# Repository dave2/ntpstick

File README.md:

ntpstick
========

NTPstick is a GPS-synced NTP server designed for low cost and ease
of deployment in places outside traditional datacentres.

The "stick" concept is that the board is expected to be placed into
a PVC tube at least 30mm I.D. with only an Ethernet cable reaching
the outside world carrying both Ethernet and poor-mans POE.

Structure
---------

This repo is divided into sections for different parts of the project:

 - hardware/ .. Contains the Kicad sources, schematics in PDF, and generated
   gerber files.
 - firmware/ .. Completed builds of the firmware, able to be flashed to 
   boards over TFTP
 - src/ .. Source code for the firmware.

Specifications
--------------

 - u.fl GPS antenna connection
 - uBlox MAX-M8Q GPS module (includes internal TCXO)
 - Atmel ATXMEGA128A4U MCU
 - 27MHz VCXO system clock
 - 12-bit DAC for VCXO control
 - WizNet W5500 Ethernet/IP chip
 - DC input on spare Ethernet pairs
 - DC-DC first stage, linear second stage PSU
 - Board is 113mm long, 30mm wide
 
License
-------

 - Please check each folder for the specific license applied, as they
   vary between sections of the project.

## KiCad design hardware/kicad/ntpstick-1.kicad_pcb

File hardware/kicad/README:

Notes on Kicad source files for NTPstick
========================================

- These files require the current upstream source of Kicad to be read.
  In general, versions shipped with most distributions are not new 
  enough to read these files. At least r5256 is required from the Kicad
  source repo.

- I have not included separate libraries or footprints that were created
  for this project. I'll include them at some future point.

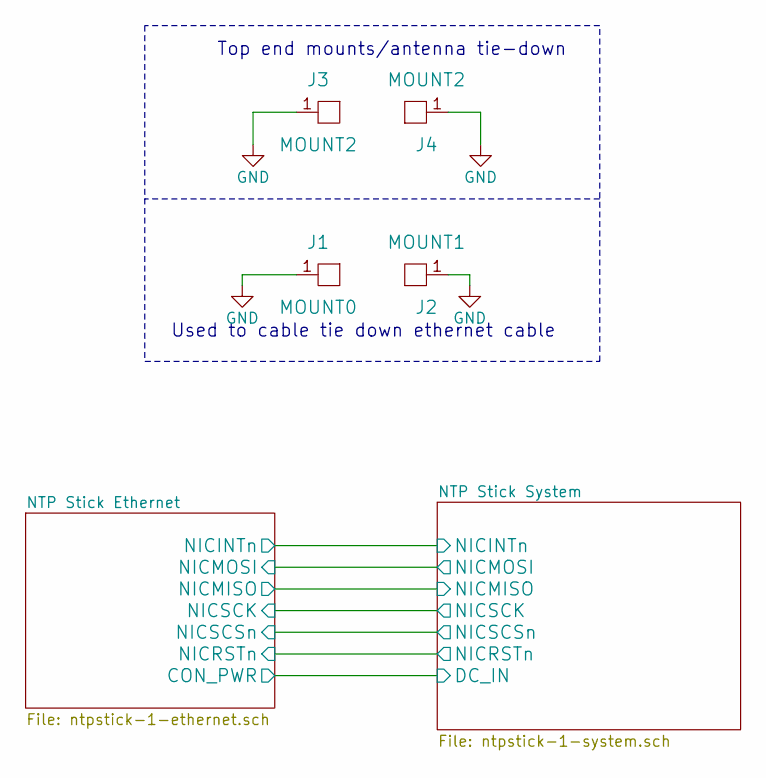
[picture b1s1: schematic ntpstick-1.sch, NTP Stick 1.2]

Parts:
J1: MOUNT0; 4-40-HOLE
J2: MOUNT1; 4-40-HOLE
J3, J4: MOUNT2; 4-40-HOLE

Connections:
GND: J1.1, J2.1, J3.1, J4.1; also elsewhere on the board

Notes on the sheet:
Used to cable tie down ethernet cable
Top end mounts/antenna tie-down

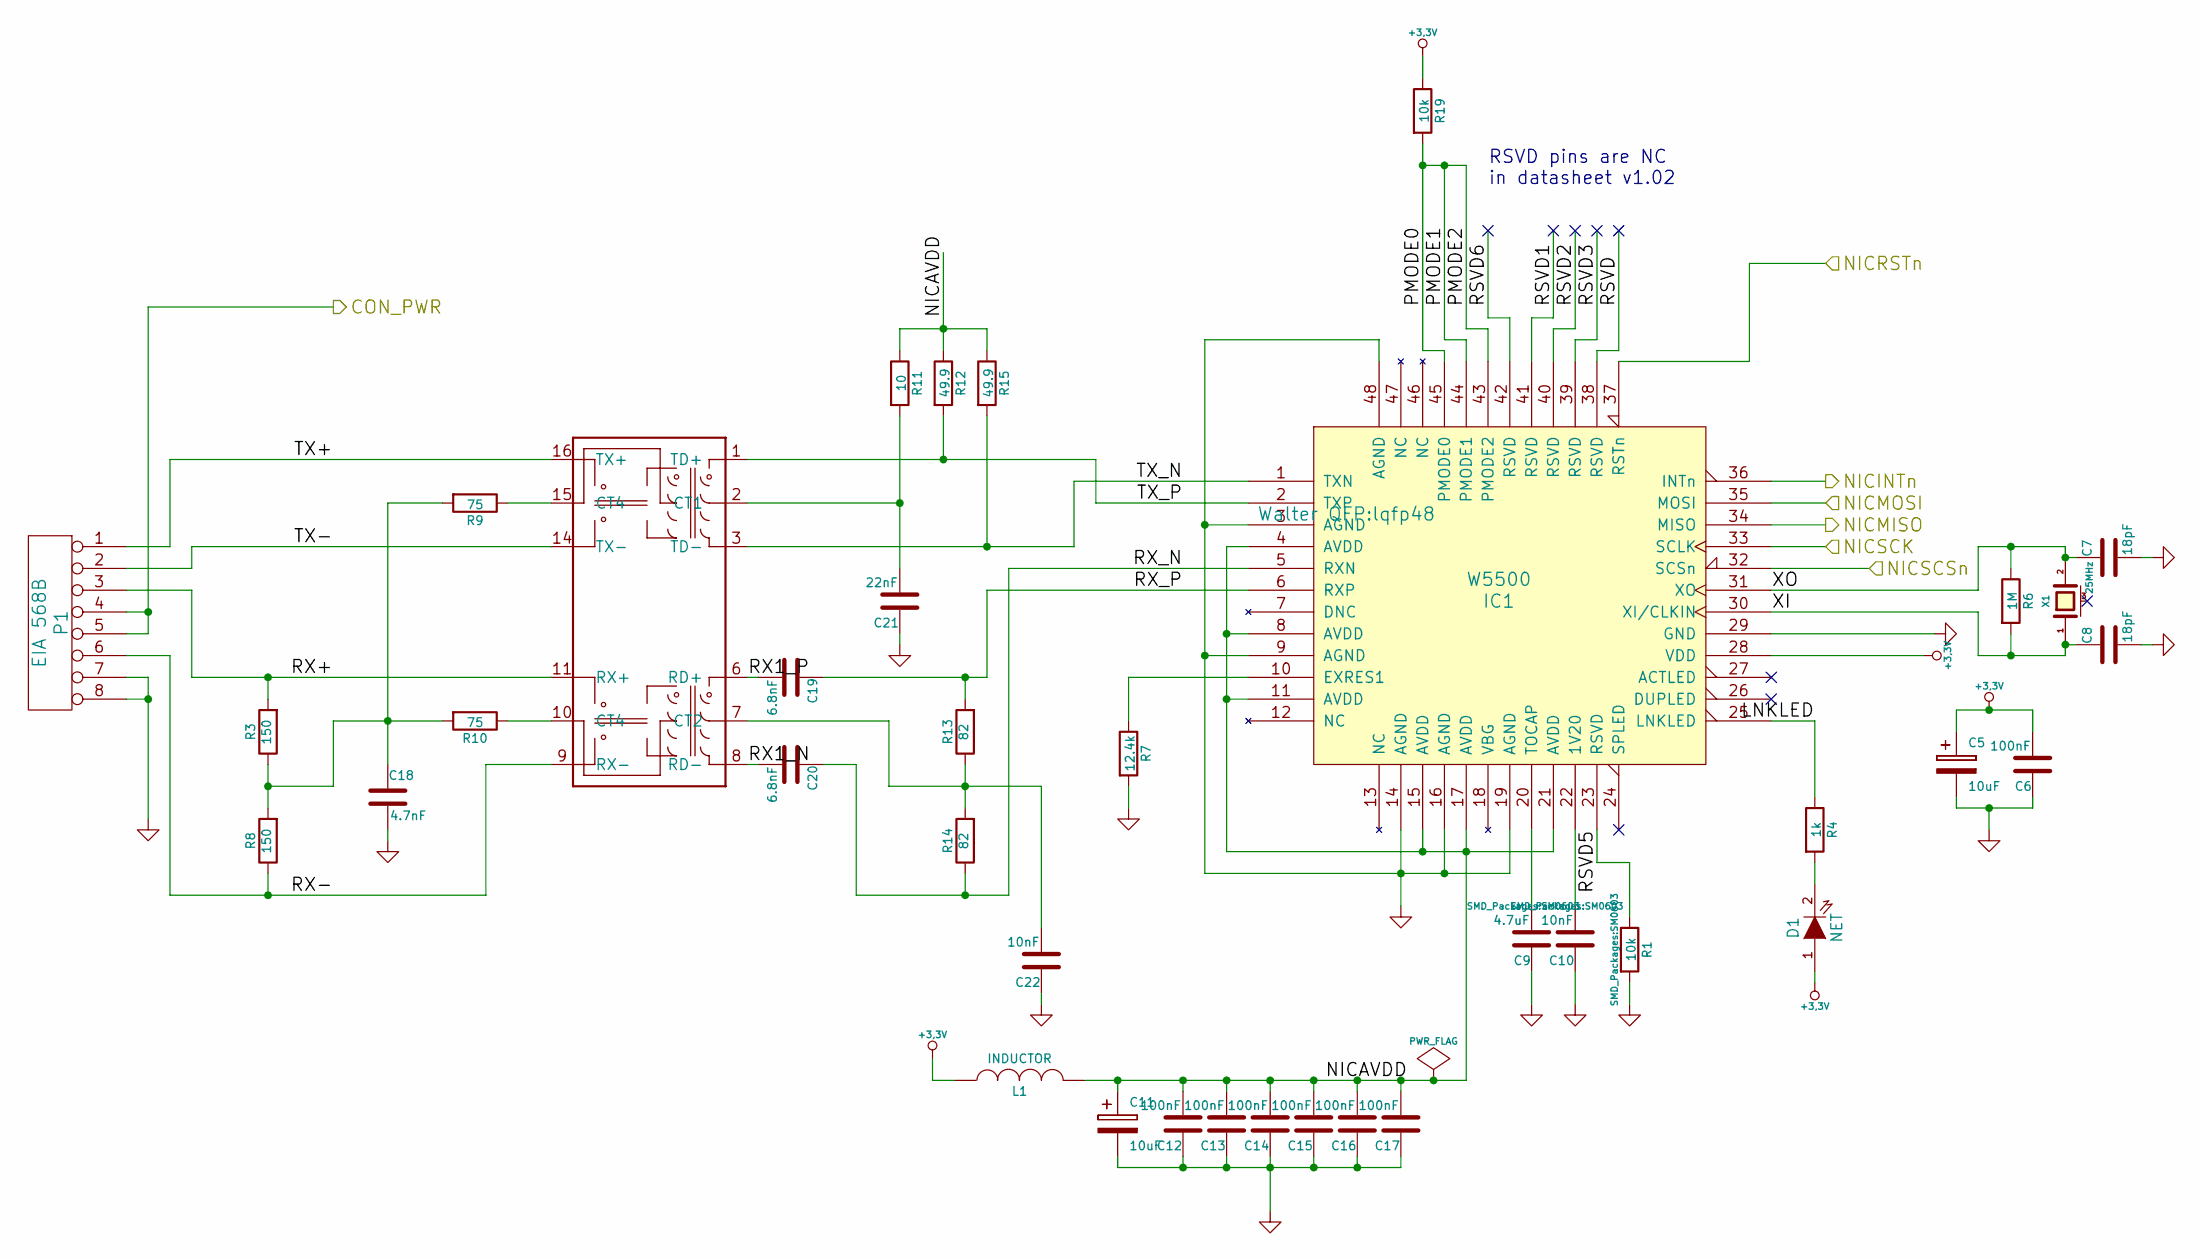
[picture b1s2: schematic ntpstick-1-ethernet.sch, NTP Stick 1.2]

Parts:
C5, C11: 10uF; c_tant_A; Voltage 16V
C6, C12, C13, C14, C15, C16, C17: 100nF; SM0603
C7, C8: 18pF; SM0603
C9: 4.7uF; SM0603
C10, C22: 10nF; SM0603
C18: 4.7nF; SM1812; Voltage 2kV
C19, C20: 6.8nF; SM0603
C21: 22nF; SM0603
D1: NET; LED-0805
IC1: W5500; lqfp48
L1: INDUCTOR; SM0603
P1: EIA 568B; pin_strip_8
R1, R19: 10k; SM0603
R3, R8: 150; SM0603
R4: 1k; SM0603
R6: 1M; SM0603
R7: 12.4k; SM0603
R9, R10: 75; SM0603
R11: 10; SM0603
R12, R15: 49.9; SM0603
R13, R14: 82; SM0603
U1: TG110-E*N5_N5; N5
X1: 25MHz; crystal_smd_5x3.2mm

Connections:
+3.3V: C5.1, C6.2, D1.1 (A), IC1.28 (VDD), L1.1, R19.1; also elsewhere on the board
/NTP Stick Ethernet/CON_PWR: P1.4, P1.5; also elsewhere on the board
/NTP Stick Ethernet/LNKLED: IC1.25 (LNKLED), R4.1
/NTP Stick Ethernet/NICAVDD: C11.1, C12.2, C13.2, C14.2, C15.2, C16.2, C17.2, IC1.4 (AVDD), IC1.8 (AVDD), IC1.11 (AVDD), IC1.15 (AVDD), IC1.17 (AVDD), IC1.21 (AVDD), L1.2, R11.1, R12.1, R15.1
/NTP Stick Ethernet/NICINTn: IC1.36 (INTn); also elsewhere on the board
/NTP Stick Ethernet/NICMISO: IC1.34 (MISO); also elsewhere on the board
/NTP Stick Ethernet/NICMOSI: IC1.35 (MOSI); also elsewhere on the board
/NTP Stick Ethernet/NICRSTn: IC1.37 (RSTn); also elsewhere on the board
/NTP Stick Ethernet/NICSCK: IC1.33 (SCLK); also elsewhere on the board
/NTP Stick Ethernet/NICSCSn: IC1.32 (SCSn); also elsewhere on the board
/NTP Stick Ethernet/PMODE0: IC1.43 (PMODE2), IC1.44 (PMODE1), IC1.45 (PMODE0), R19.2
/NTP Stick Ethernet/RSVD: IC1.38 (RSVD)
/NTP Stick Ethernet/RSVD1: IC1.41 (RSVD)
/NTP Stick Ethernet/RSVD2: IC1.40 (RSVD)
/NTP Stick Ethernet/RSVD3: IC1.39 (RSVD)
/NTP Stick Ethernet/RSVD5: IC1.23 (RSVD), R1.1
/NTP Stick Ethernet/RSVD6: IC1.42 (RSVD)
/NTP Stick Ethernet/RX1_N: C20.2, U1.8 (RD-)
/NTP Stick Ethernet/RX1_P: C19.2, U1.6 (RD+)
/NTP Stick Ethernet/RX+: P1.3, R3.2, U1.11 (RX+)
/NTP Stick Ethernet/RX-: P1.6, R8.1, U1.9 (RX-)
/NTP Stick Ethernet/RX_N: C20.1, IC1.5 (RXN), R14.1
/NTP Stick Ethernet/RX_P: C19.1, IC1.6 (RXP), R13.2
/NTP Stick Ethernet/TX+: P1.1, U1.16 (TX+)
/NTP Stick Ethernet/TX-: P1.2, U1.14 (TX-)
/NTP Stick Ethernet/TX_N: IC1.1 (TXN), R15.2, U1.3 (TD-)
/NTP Stick Ethernet/TX_P: IC1.2 (TXP), R12.2, U1.1 (TD+)
/NTP Stick Ethernet/XI: C8.1, IC1.30 (XI/CLKIN), R6.2, X1.1
/NTP Stick Ethernet/XO: C7.1, IC1.31 (XO), R6.1, X1.2
GND: C5.2, C6.1, C7.2, C8.2, C9.1, C10.1, C11.2, C12.1, C13.1, C14.1, C15.1, C16.1, C17.1, C18.2, C21.1, C22.1, IC1.3 (AGND), IC1.9 (AGND), IC1.14 (AGND), IC1.16 (AGND), IC1.19 (AGND), IC1.29 (GND), IC1.48 (AGND), P1.7, P1.8, R1.2, R7.2; also elsewhere on the board
unnamed: C9.2, IC1.20 (TOCAP)
unnamed: C10.2, IC1.22 (1V20)
unnamed: C18.1, R3.1, R8.2, R9.2, R10.2
unnamed: C21.2, R11.2, U1.2 (CT1)
unnamed: C22.2, R13.1, R14.2, U1.7 (CT2)
unnamed: D1.2 (K), R4.2
unnamed: IC1.10 (EXRES1), R7.1
unnamed: R9.1, U1.15 (CT4)
unnamed: R10.1, U1.10 (CT4)

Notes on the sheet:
RSVD pins are NC in datasheet v1.02

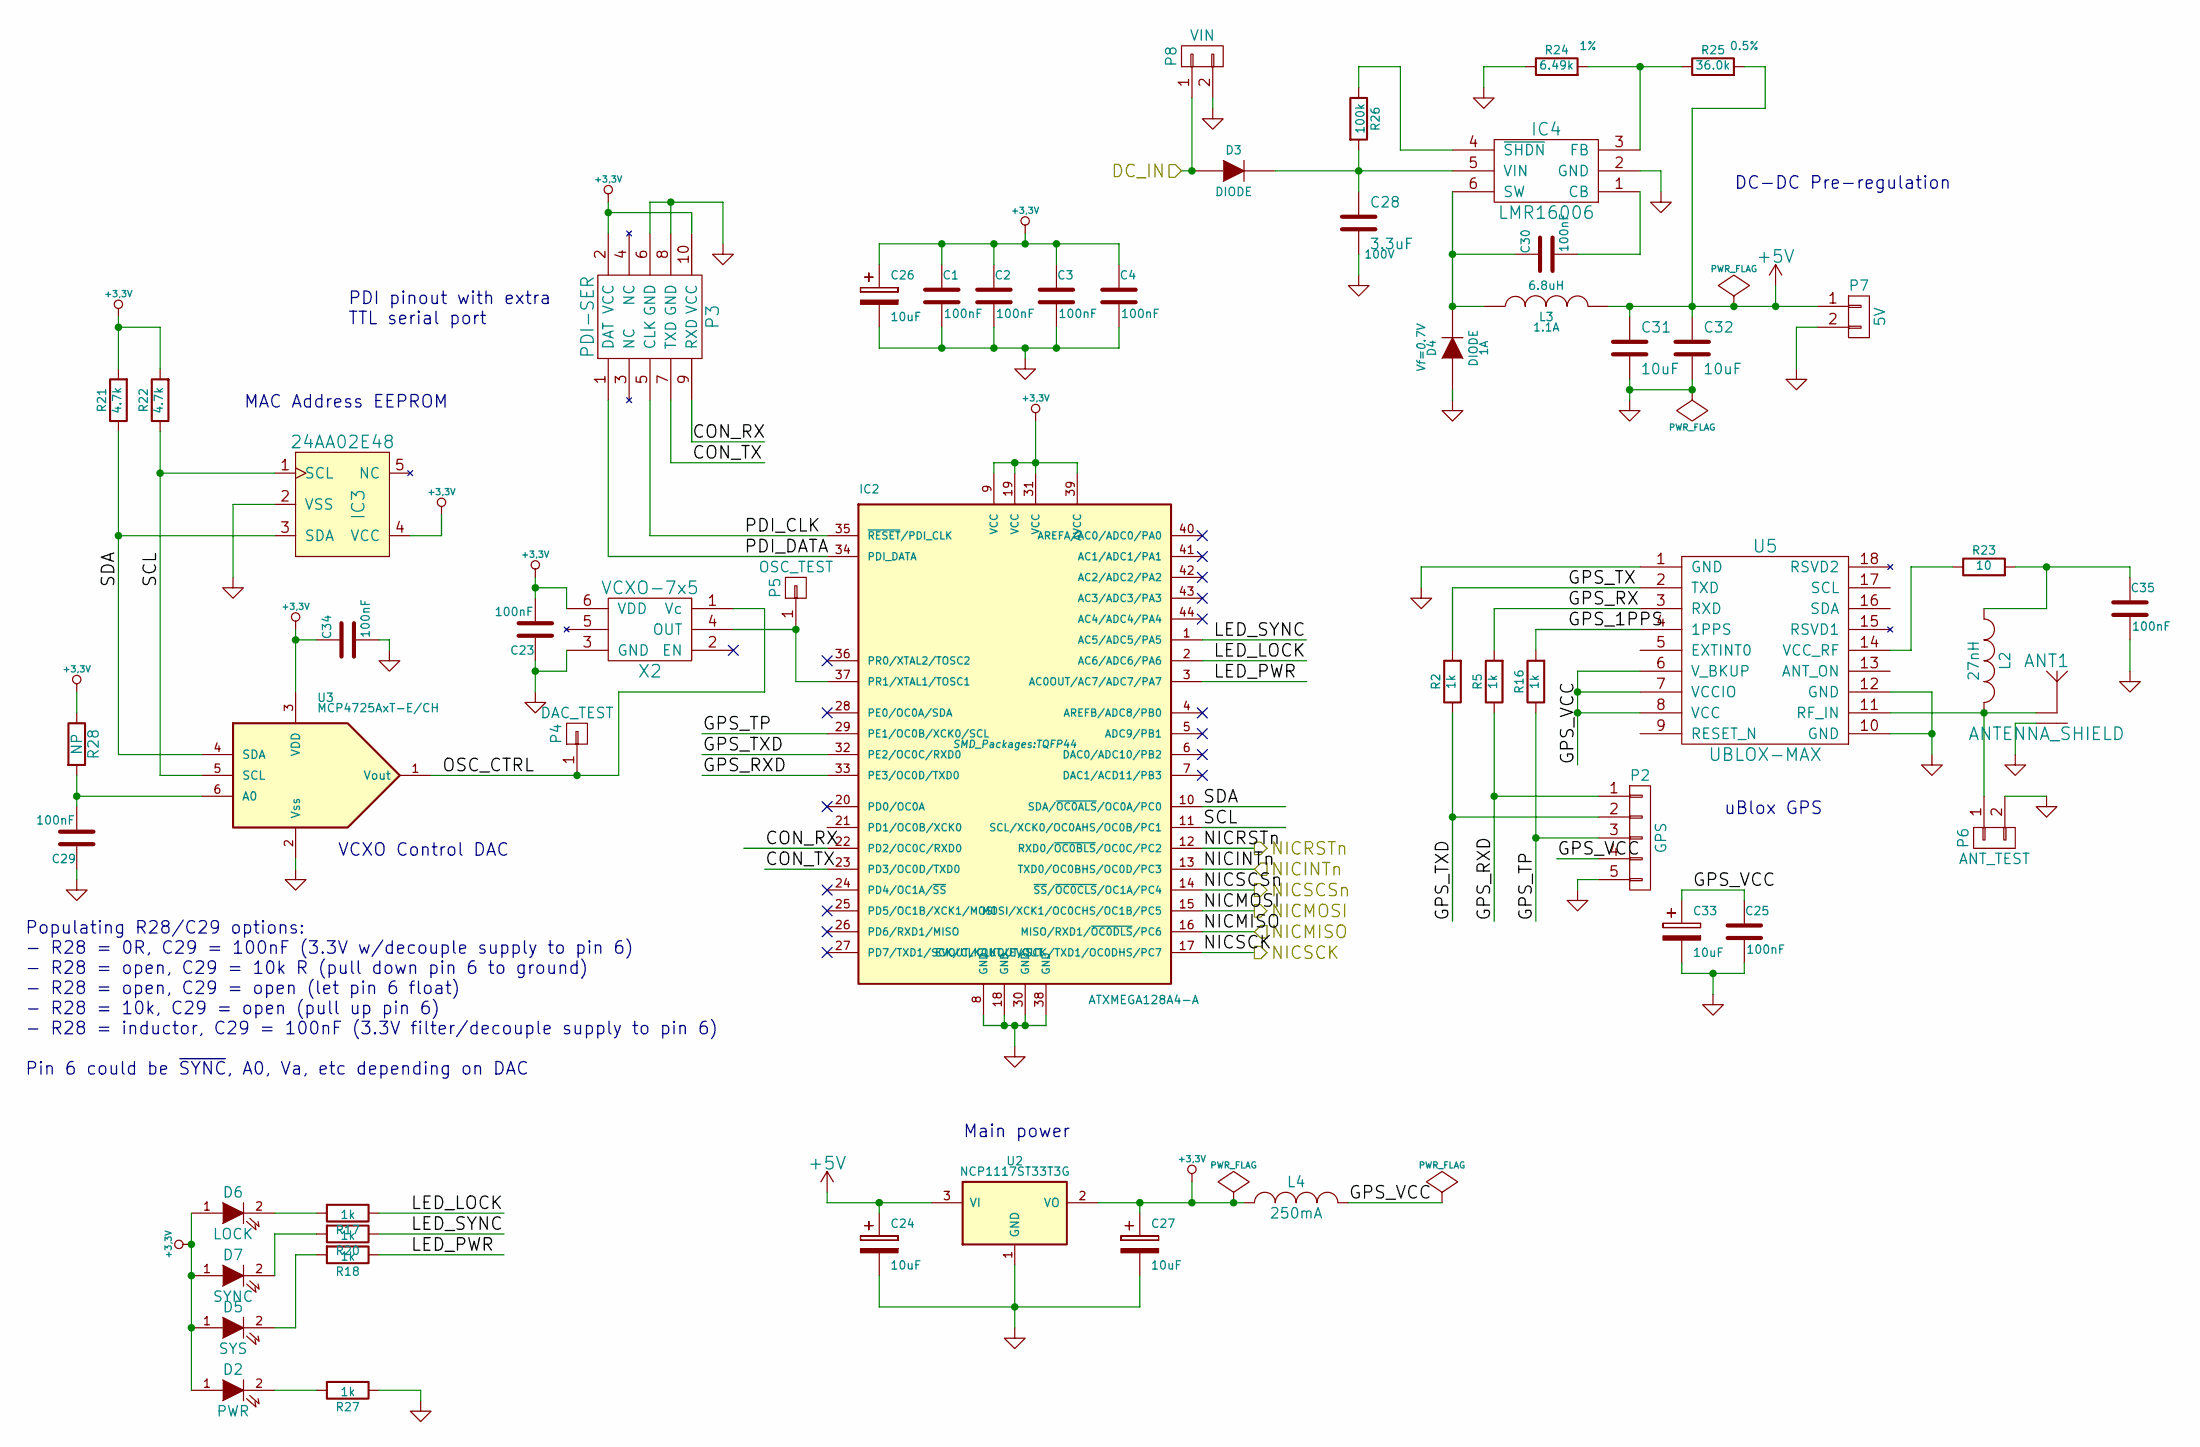
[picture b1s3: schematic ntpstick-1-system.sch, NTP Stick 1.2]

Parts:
ANT1: ANTENNA_SHIELD; coaxial_u.fl-r-smt-1
C1, C2, C3, C4, C23, C25, C29, C30, C34, C35: 100nF; SM0603
C24, C26, C27, C33: 10uF; c_tant_A; Voltage 16V
C28: 3.3uF; SM1210; Voltage 100V
C31, C32: 10uF; c_1206
D2: PWR; LED-0805
D3, D4: DIODE; do214ac
D5: SYS; LED-0805
D6: LOCK; LED-0805
D7: SYNC; LED-0805
IC2: ATXMEGA128A4-A; TQFP44
IC3: 24AA02E48; SOT23-5
IC4: LMR16006; SOT23_6
L2: 27nH; SM0603
L3: 6.8uH; inductor_bourns_srn5040
L4: 250mA; SM0603
P2: GPS; Pin_Header_Straight_1x05
P3: PDI-SER; Pin_Header_Straight_2x05
P4: DAC_TEST; Measurement_Point_Round-SMD-Pad_Small
P5: OSC_TEST; Measurement_Point_Round-SMD-Pad_Small
P6: ANT_TEST; Pin_Header_Straight_1x02
P7: 5V; Pin_Header_Straight_1x02
P8: VIN; Pin_Header_Straight_1x02
R2, R5, R16, R17, R18, R20, R27: 1k; SM0603
R21, R22: 4.7k; SM0603
R23: 10; SM0603
R24: 6.49k; SM0603
R25: 36.0k; SM0603
R26: 100k; SM0603
R28: NP; SM0603
U2: NCP1117ST33T3G; SOT223
U3: MCP4725AxT-E/CH; SOT23_6
U5: UBLOX-MAX; UBLOX-MAX-8-POLY
X2: VCXO-7x5; vcxo-7x5

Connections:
+3.3V: C1.1, C2.1, C3.1, C4.1, C23.2, C26.1, C27.1, C34.1, D2.1 (A), D5.1 (A), D6.1 (A), D7.1 (A), IC2.9 (VCC), IC2.19 (VCC), IC2.31 (VCC), IC2.39 (AVCC), IC3.4 (VCC), L4.1, P3.2 (VCC), P3.10 (VCC), R21.2, R22.2, R28.1, U2.2 (VO), U3.3 (VDD), X2.6 (VDD); also elsewhere on the board
+5V: C24.1, C31.1, C32.1, L3.2, P7.1, R25.2, U2.3 (VI)
/NTP Stick Ethernet/CON_PWR: D3.1 (A), P8.1; also elsewhere on the board
/NTP Stick Ethernet/NICINTn: IC2.13 (TXD0/OC0BHS/OC0D/PC3); also elsewhere on the board
/NTP Stick Ethernet/NICMISO: IC2.16 (MISO/RXD1/~OC0DLS~/PC6); also elsewhere on the board
/NTP Stick Ethernet/NICMOSI: IC2.15 (MOSI/XCK1/OC0CHS/OC1B/PC5); also elsewhere on the board
/NTP Stick Ethernet/NICRSTn: IC2.12 (RXD0/~OC0BLS~/OC0C/PC2); also elsewhere on the board
/NTP Stick Ethernet/NICSCK: IC2.17 (EVOUT/CLKOUT/SCK/TXD1/OC0DHS/PC7); also elsewhere on the board
/NTP Stick Ethernet/NICSCSn: IC2.14 (~SS~/~OC0CLS~/OC1A/PC4); also elsewhere on the board
/NTP Stick System/CON_RX: IC2.22 (PD2/OC0C/RXD0), P3.9 (RXD)
/NTP Stick System/CON_TX: IC2.23 (PD3/OC0D/TXD0), P3.7 (TXD)
/NTP Stick System/GPS_1PPS: R16.2, U5.4 (1PPS)
/NTP Stick System/GPS_RX: R5.2, U5.3 (RXD)
/NTP Stick System/GPS_RXD: IC2.33 (PE3/OC0D/TXD0), P2.1, R5.1
/NTP Stick System/GPS_TP: IC2.29 (PE1/OC0B/XCK0/SCL), P2.3, R16.1
/NTP Stick System/GPS_TX: R2.2, U5.2 (TXD)
/NTP Stick System/GPS_TXD: IC2.32 (PE2/OC0C/RXD0), P2.2, R2.1
/NTP Stick System/GPS_VCC: C25.1, C33.1, L4.2, P2.4, U5.6 (V_BKUP), U5.7 (VCCIO), U5.8 (VCC)
/NTP Stick System/LED_LOCK: IC2.2 (AC6/ADC6/PA6), R17.1
/NTP Stick System/LED_PWR: IC2.3 (AC0OUT/AC7/ADC7/PA7), R18.1
/NTP Stick System/LED_SYNC: IC2.1 (AC5/ADC5/PA5), R20.1
/NTP Stick System/OSC_CTRL: P4.1, U3.1 (Vout), X2.1 (Vc)
/NTP Stick System/PDI_CLK: IC2.35 (~RESET~/PDI_CLK), P3.5 (CLK)
/NTP Stick System/PDI_DATA: IC2.34 (PDI_DATA), P3.1 (DAT)
/NTP Stick System/SCL: IC2.11 (SCL/XCK0/OC0AHS/OC0B/PC1), IC3.1 (SCL), R22.1, U3.5 (SCL)
/NTP Stick System/SDA: IC2.10 (SDA/~OC0ALS~/OC0A/PC0), IC3.3 (SDA), R21.1, U3.4 (SDA)
GND: ANT1.2, C1.2, C2.2, C3.2, C4.2, C23.1, C24.2, C25.2, C26.2, C27.2, C28.2, C29.1, C31.2, C32.2, C33.2, C34.2, C35.2, D4.1 (A), IC2.8 (GND), IC2.18 (GND), IC2.30 (GND), IC2.38 (GND), IC3.2 (VSS), IC4.2 (GND), P2.5, P3.6 (GND), P3.8 (GND), P6.2, P7.2, P8.2, R24.1, R27.1, U2.1 (GND), U3.2 (Vss), U5.1 (GND), U5.10 (GND), U5.12 (GND), X2.3 (GND); also elsewhere on the board
unnamed: ANT1.1, L2.2, P6.1, U5.11 (RF_IN)
unnamed: C28.1, D3.2 (K), IC4.5 (VIN), R26.2
unnamed: C29.2, R28.2, U3.6 (A0)
unnamed: C30.1, D4.2 (K), IC4.6 (SW), L3.1
unnamed: C30.2, IC4.1 (CB)
unnamed: C35.1, L2.1, R23.2
unnamed: D2.2 (K), R27.2
unnamed: D5.2 (K), R18.2
unnamed: D6.2 (K), R17.2
unnamed: D7.2 (K), R20.2
unnamed: IC2.37 (PR1/XTAL1/TOSC1), P5.1, X2.4 (OUT)
unnamed: IC4.3 (FB), R24.2, R25.1
unnamed: IC4.4 (~SHDN~), R26.1
unnamed: R23.1, U5.14 (VCC_RF)

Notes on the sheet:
MAC Address EEPROM
VCXO Control DAC
DC-DC Pre-regulation
PDI pinout with extra TTL serial port
Main power
uBlox GPS
Populating R28/C29 options: - R28 = 0R, C29 = 100nF (3.3V w/decouple supply to pin 6) - R28 = open, C29 = 10k R (pull down pin 6 to ground) - R28 = open, C29 = open (let pin 6 float) - R28 = 10k, C29 = open (pull up pin 6) - R28 = inductor, C29 = 100nF (3.3V filter/decouple supply to pin 6) Pin 6 c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

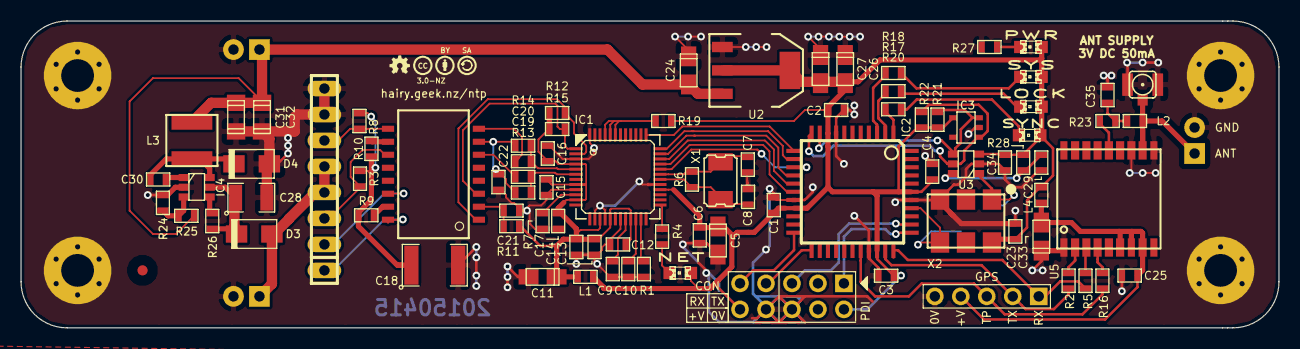
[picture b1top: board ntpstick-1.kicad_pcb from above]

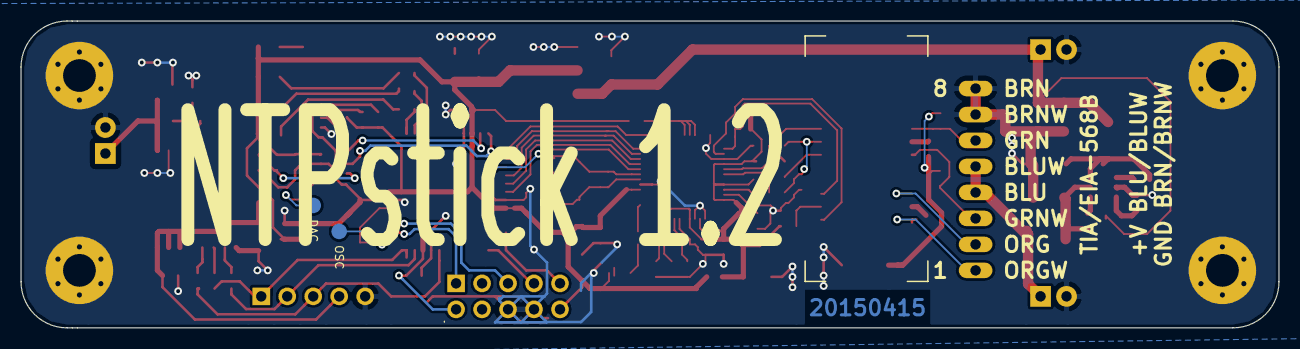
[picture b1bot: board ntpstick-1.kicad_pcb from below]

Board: 2 copper layers, 123.0 x 30.0 mm, 103 parts (3 on the bottom side), 66 nets.

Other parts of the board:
FIDUCIAL: val**; FIDUCIAL
LOGO_CC: VAL**; LOGO_CC_1.9mm
LOGO_CC_BY: VAL**; LOGO_CC_BY_1.9mm
LOGO_CC_SA: VAL**; LOGO_CC_SA_1.9mm
LOGO_OSHW_silkscreen_2mm: val**; LOGO_OSHW_silkscreen_2mm
SERIAL_LABEL: VAL**; SERIAL_LABEL

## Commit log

2014-11-10 Add more details about the project
2014-11-10 Clean up .gitignore, removing some files which will be required for hardware design.
2014-11-10 Initial cut of hardware source files
2014-11-10 Gerbers most recently generated.
2014-11-10 License and README for gerbers
2014-11-10 License and README for Kicad Source files
2014-11-10 Add schematic as PDF
2014-11-10 Also add some details on structure
2014-11-10 How about some dimensions as well.
2014-11-11 Gerbers sent for panelisation on 20141111
2014-11-11 libkakapo base for ntpstick development Explanation of source structure and build requirements
2014-11-11 Fix some typos in ntpstick source readme
2014-11-11 Really simple hack to build libkakapo and then ntpstick objects
2014-11-14 Add codeblocks stuff to ignore filter
2014-11-15 Inital rough test of console over serial.
2014-11-16 Network config, eeprom setup, provide firmware build date in boot scrawl
2014-11-16 Very rudimentary console over telnet support. Not fully working yet.
2014-12-13 Add initial breakout of telnetd support, incl. commands
2014-12-13 Switch to single event handler in driver code. This resyncs us with libkakapo mainline
2014-12-13 Various changes, mostly around getting telnetd working.
2015-01-24 Many changes. Such progress. Wow.
2015-02-06 Resync to libkakapo upstream. More hacking on MAX580X DAC.
2015-02-06 Remove TWI code that was being reworked now it's in libkakapo mainline.
2015-03-21 Resync libkakapo copy with v0.2 interim release.
2015-03-24 Another re-sync with libkakapo (somewhere after 0.2.1)
2015-03-26 Stuff. Things. I should document my changes better.
2015-03-29 Version 1.2 HW design
2015-03-29 Update specs to current
2015-03-29 Fix up 1.2 schematics
2015-09-10 Remove schematic file no longer used
2015-09-10 Final manufactured version of 1.2 HW
2015-09-10 Gerbers for HW 1.2 actually manufactured
2015-09-10 Remove extra schematic copy that slipped in at some stage
2015-09-10 Update 1.2 HW schematic to final version
2015-09-10 Include initial PNP position data output from 1.2 final HW
